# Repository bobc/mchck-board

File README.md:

About BC-HCK
============

Originally derived from mchck project. I simplified the design a lot to make more of
a bare bones board, and extended the size to get more pins at the edge.
I also incorporated ideas from TinyK20 board, the pin layout is similar (https://github.com/ErichStyger/mcuoneclipse/tree/master/tinyK20).

The schematic design and layout was done using Kicad, a Free Software EDA tool for Linux, Windows and Mac OS (http://kicad-pcb.org/download/). You will need KiCad to open the files - gEDA or Eagle will not work.

Note: this project needs the new stable version of Kicad (4.0.0 or later), previous versions can not read the new files.

Copyright
---------
In keeping with original project, licensed with CERN OHL.

Copyright (c) 2016 Bob Cousins  
Copyright (c) 2011,2012 Simon Schubert <2@0x2c.org>

This documentation describes Open Hardware and is licensed under the
CERN OHL v. 1.1.  You may redistribute and modify this documentation
under the terms of the CERN OHL v.1.1.  You can find a copy of the
CERN OHL v.1.1 in the file LICENSE.

Fabrication outputs
-------------------

The gerbers are in the master branch in the gerbers folder.  
The zip file is for submission to ITeadMall, probably could be used for other fab houses.  
The gvp file is for use with gerbv (http://gerbv.geda-project.org/).

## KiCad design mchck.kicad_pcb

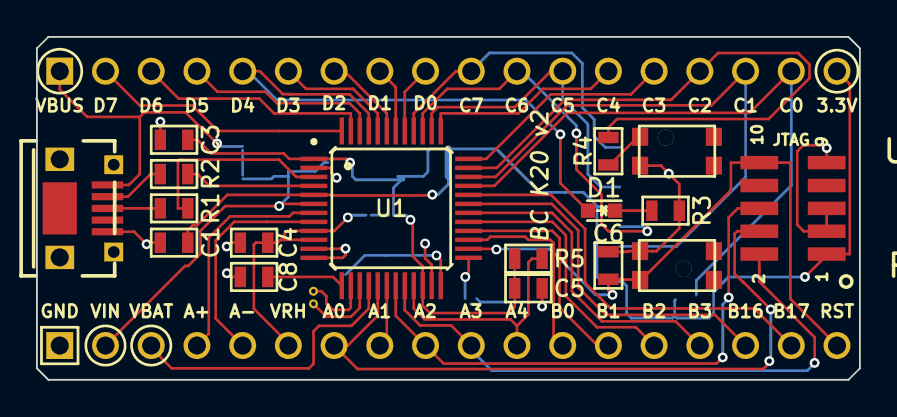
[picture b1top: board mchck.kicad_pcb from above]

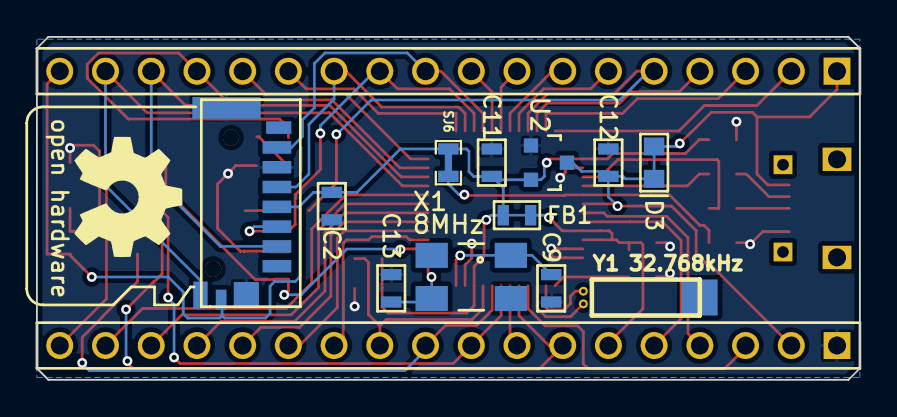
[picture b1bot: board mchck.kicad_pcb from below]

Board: 2 copper layers, 45.7 x 19.1 mm, 32 parts (15 on the bottom side), 48 nets.

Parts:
C1: 2.2u; SM0603_Capa
C2, C3, C4, C5, C6, C8: 100n; SM0603_Capa
C9, C13: 18pF; SM0603_Capa
C11, C12: 10u; SM0603_Capa
D1: LED; LED-0603
D3: DIODE-SCHOTTKY_; SOD-523F-NC
FB1: FILTER; SM0603_NC
G1: OHW LOGO; OHW-LOGO-6mm
J3: MICRO_USB; USB_MICRO_RMC_FCI
K1: CONN_MICROSD; SD_MOLEX_47579-0001-2
P3: UPPER_PINS; pin_header_2.54mm_1x18
P4: LOWER_PINS; pin_header_2.54mm_1x18
P6: JTAG; Pin_Array_5x2_SMT_1.27mm_RMC
R1, R2: 33; SM0603
R3: 1k; SM0603
R4, R5: 10k; SM0603
S1: RESET; SW_C&K_KMR4_ALT
S2: USER; SW_C&K_KMR4_ALT
SJ6: SOLDERJUMPERNC; SM0603_Bridged
U1: MK20LF; LQFP48
U2: MCP1703_SOT23; SOT-23
X1: 8MHz; Crystal_SMD_0603_4Pads
Y1: 32.768kHz; crystal_tc-26_horiz

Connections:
/MCU/A18: C9.1, U1.24, X1.1
/MCU/A19: C13.1, U1.25, X1.3
/USB/USB_D+: J3.3, R1.1
/USB/USB_D-: J3.2, R2.1
A0: P4.7, P6.4, U1.17
A1: P4.8, U1.18
A2: P4.9, P6.6, U1.19
A3: P4.10, P6.2, U1.20
A4: P4.11, R5.2, U1.21
ADC0+: P4.4, U1.7
ADC0-: P4.5, U1.8
B0: P4.12, U1.27
B1: P4.13, U1.28
B2: P4.14, U1.29
B3: P4.15, U1.30
B16: P4.16, U1.31
B17: P4.17, U1.32
C0: K1.11, P3.17, U1.33
C1: K1.2, P3.16, U1.34
C2: P3.15, R4.1, U1.35
C3: P3.14, U1.36
C4: P3.13, U1.37
C5: K1.5, P3.12, U1.38
C6: K1.3, P3.11, U1.39
C7: K1.7, P3.10, U1.40
D0: P3.9, U1.41
D1: P3.8, U1.42
D2: P3.7, U1.43
D3: P3.6, U1.44
D4: D1.2, P3.5, U1.45
D5: P3.4, U1.46
D6: P3.3, U1.47
D7: P3.2, U1.48
GND: C1.2, C2.2, C3.2, C4.2, C5.2, C6.2, C8.2, C9.2, C11.2, C12.2, C13.2, J3.4, K1.6, K1.9, P4.1, P6.3, P6.5, P6.9, R3.2, S1.4, S2.2, U1.2, U1.11, U1.12, U1.23, U2.1
unnamed: C8.1, U1.13
unnamed: D1.1, R3.1
unnamed: R4.2, S2.1
unnamed: U1.14, Y1.2
unnamed: U1.15, Y1.1
RST: C6.1, P4.18, P6.10, S1.3, U1.26
USB_DM: R2.2, U1.4
USB_DP: R1.2, U1.3
VBAT: P4.3, U1.16
VBUS: D3.A, J3.1, P3.1
VDD: C2.1, C3.1, C5.1, C11.1, FB1.1, K1.4, K1.10, P3.18, P6.1, R5.1, SJ6.2, U1.1, U1.22, U2.2
VRAW: C12.1, D3.C, P4.2, U1.6, U2.3
VREFH: C4.1, FB1.2, P4.6, U1.9, U1.10
VREG_K20: C1.1, SJ6.1, U1.5

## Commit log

2015-12-14 Mash up of MCHCK with TinyK20-like pinout
2015-12-20 Move standard schematic libraries to library folder
2016-01-01 Allow some file types
2016-01-01 Fix up libs and footprints for Kicad v4; remove several unused libs
2016-01-01 Remove .cmp file, no longer used
2016-01-01 Add missing schematic libs
2016-01-01 Add missing footprints; convert for Kicad v4
2016-01-01 Add gerber files
2016-01-01 Move script files to tools
2016-01-01 Remove some unused files
2016-01-01 Remove the rescue lib (no longer used)
2016-01-01 Move script file to tools
2016-01-01 Tidy up some texts; add doc files
2016-01-01 Add 3d model for IC
2016-01-01 Add KiCad badge
2016-01-03 Final tidy up for V2.
2016-02-17 Added BOMs for popular suppliers

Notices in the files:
mchck.kicad_pcb:
(c) 2011,2012,2013 Simon Schubert
CERN OHL v.1.1 or later
